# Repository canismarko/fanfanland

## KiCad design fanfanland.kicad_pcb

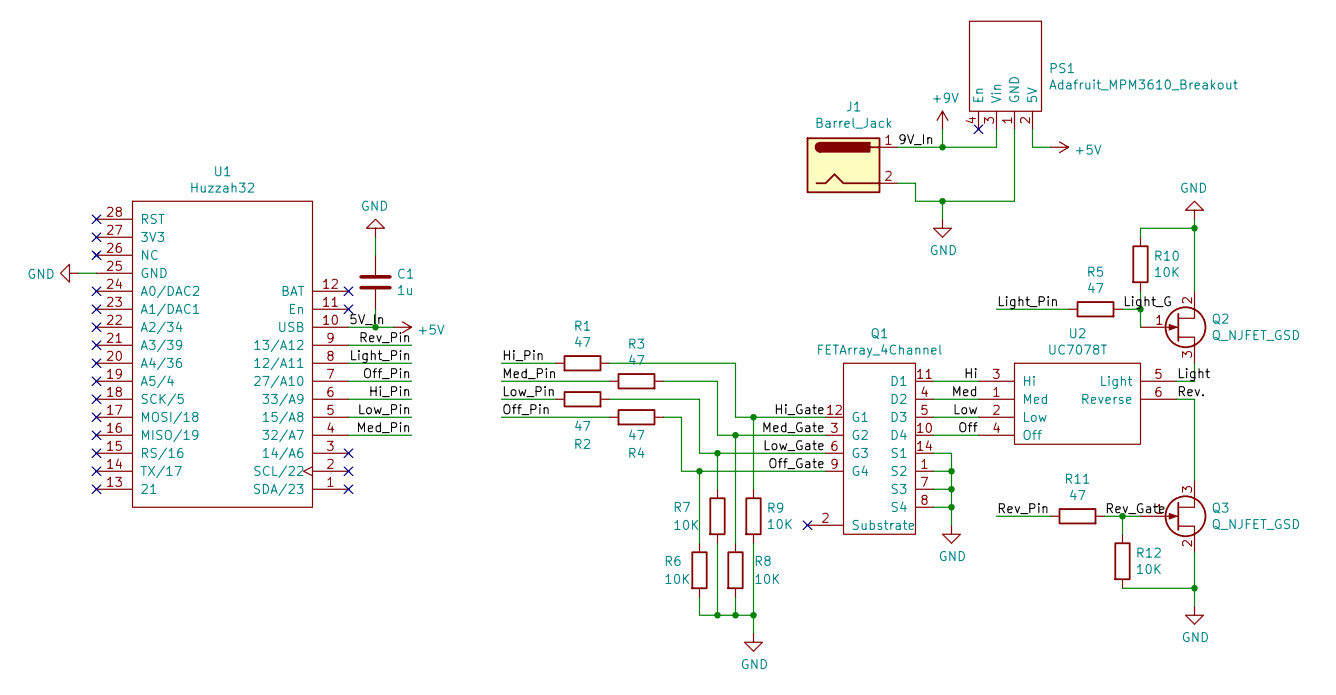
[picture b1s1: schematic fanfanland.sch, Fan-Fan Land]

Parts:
C1: 1u; C_1206_HandSoldering
J1: Barrel_Jack; 1X02
PS1: Adafruit_MPM3610_Breakout; MPM3610_Buck_Convertor_Breakout
Q1: FETArray_4Channel; SOIC-14_3.9x8.7mm_Pitch1.27mm
Q2, Q3: Q_NJFET_GSD; SOT-23_Handsoldering
R1, R2, R3, R4, R5, R11: 47; C_1206_HandSoldering
R6, R7, R8, R9, R10, R12: 10K; C_1206_HandSoldering
U1: Huzzah32; PCB_FeatherWing
U2: UC7078T; 1X06

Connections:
+5V: C1.2, PS1.2 (5V), U1.10 (USB)
+9V: J1.1, PS1.3 (Vin)
/Hi: Q1.11 (D1), U2.3 (Hi)
/Hi_Gate: Q1.12 (G1), R1.1, R9.1
/Hi_Pin: R1.2, U1.6 (33/A9)
/Light: Q2.3 (D), U2.5 (Light)
/Light_G: Q2.1 (G), R5.2, R10.2
/Light_Pin: R5.1, U1.8 (12/A11)
/Low: Q1.5 (D3), U2.2 (Low)
/Low_Gate: Q1.6 (G3), R2.2, R7.1
/Low_Pin: R2.1, U1.5 (15/A8)
/Med: Q1.4 (D2), U2.1 (Med)
/Med_Gate: Q1.3 (G2), R3.2, R8.1
/Med_Pin: R3.1, U1.4 (32/A7)
/Off: Q1.10 (D4), U2.4 (Off)
/Off_Gate: Q1.9 (G4), R4.1, R6.1
/Off_Pin: R4.2, U1.7 (27/A10)
/Rev.: Q3.3 (S), U2.6 (Reverse)
/Rev_Gate: Q3.1 (G), R11.2, R12.1
/Rev_Pin: R11.1, U1.9 (13/A12)
GND: C1.1, J1.2, PS1.1 (GND), Q1.1 (S2), Q1.7 (S3), Q1.8 (S4), Q1.14 (S1), Q2.2 (S), Q3.2 (D), R6.2, R7.2, R8.2, R9.2, R10.1, R12.2, U1.25 (GND)

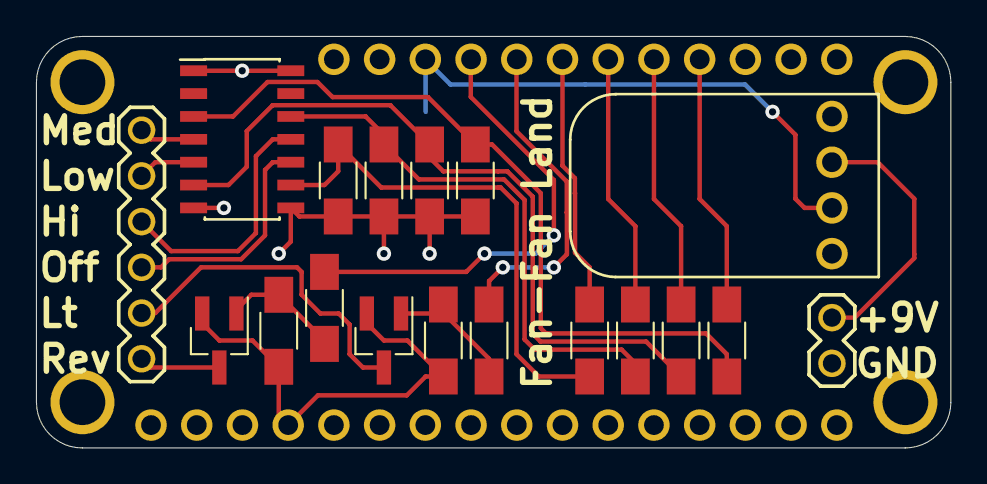
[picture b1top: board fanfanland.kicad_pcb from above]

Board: 2 copper layers, 50.8 x 22.9 mm, 20 parts (1 on the bottom side), 21 nets.

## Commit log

2021-05-06 First round of PCB design.
2021-05-06 Basic YAML file for esphome.
2021-05-06 Added PCB gerber files for fabiraction and .gitignore file.
2021-05-15 Built the first version and added ESPHOME config for fan and light.
